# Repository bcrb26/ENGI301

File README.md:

# ENGI301
# "Repository for ENGI301 course work"
# PROJECT BAKI 
# woohoo
# Breakthrough Automated [Redacted] Instrument

# I forgot how to use github lol

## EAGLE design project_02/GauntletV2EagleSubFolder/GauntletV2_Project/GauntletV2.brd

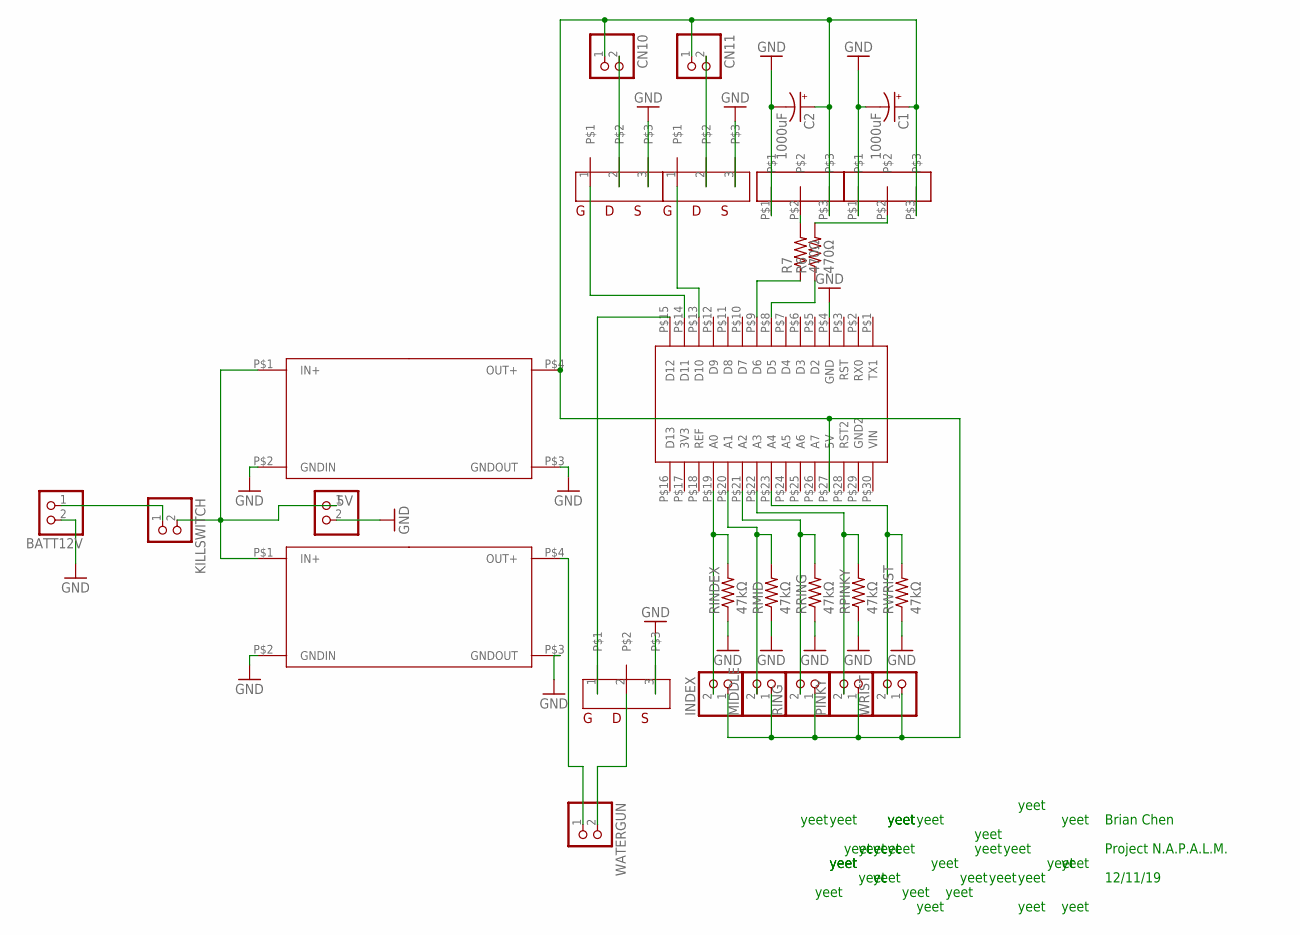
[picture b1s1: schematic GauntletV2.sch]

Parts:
5VBUCK, 6VBUCK: LM2596BUCK
BATT12V: JST_2PIN-THM-RA; JST-PH-2-THM-RA
C1, C2: 1000uF; E5-10,5
CN10, CN11: JST_2PIN-THM-RA; JST-PH-2-THM-RA
GUNMOSFET: TO254P1052X465X1989-3
INDEX: JST_2PIN-THM-RA; JST-PH-2-THM-RA
KILLSWITCH: JST_2PIN-THM-RA; JST-PH-2-THM-RA
MIDDLE: JST_2PIN-THM-RA; JST-PH-2-THM-RA
NANO: NANOV3
PINKY: JST_2PIN-THM-RA; JST-PH-2-THM-RA
R6, R7: 470Ω; 0207/9
RINDEX: 47kΩ; 0207/9
RING: JST_2PIN-THM-RA; JST-PH-2-THM-RA
RMID: 47kΩ; 0207/9
RPINKY: 47kΩ; 0207/9
RRING: 47kΩ; 0207/9
RWRIST: 47kΩ; 0207/9
U$4, U$5: TO254P1052X465X1989-3
U$7, U$8: 3WIRECONNECTOR
VOLTMETER: JST_2PIN-THM-RA; JST-PH-2-THM-RA
WATERGUN: JST_2PIN-THM-RA; JST-PH-2-THM-RA
WRIST: JST_2PIN-THM-RA; JST-PH-2-THM-RA

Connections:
5V: 5VBUCK.P$1 (IN+), 6VBUCK.P$1 (IN+), KILLSWITCH.2 (1), VOLTMETER.1 (2)
GND: 5VBUCK.P$2 (GNDIN), 5VBUCK.P$3 (GNDOUT), 6VBUCK.P$2 (GNDIN), 6VBUCK.P$3 (GNDOUT), BATT12V.2 (1), C1.-, C2.-, GUNMOSFET.3, NANO.P$4 (GND), RINDEX.1, RMID.1, RPINKY.1, RRING.1, RWRIST.1, U$4.3, U$5.3, U$7.P$1, U$8.P$1, VOLTMETER.2 (1)
unnamed: BATT12V.1 (2), KILLSWITCH.1 (2)
unnamed: 5VBUCK.P$4 (OUT+), C1.+, C2.+, CN10.1 (2), CN11.1 (2), INDEX.1 (2), MIDDLE.1 (2), NANO.P$27 (5V), PINKY.1 (2), RING.1 (2), U$7.P$3, U$8.P$3, WRIST.1 (2)
unnamed: R7.2, U$7.P$2
unnamed: GUNMOSFET.2, WATERGUN.2 (1)
unnamed: 6VBUCK.P$4 (OUT+), WATERGUN.1 (2)
unnamed: GUNMOSFET.1, NANO.P$15 (D12)
unnamed: INDEX.2 (1), NANO.P$19 (A0), RINDEX.2
unnamed: NANO.P$23 (A4), RWRIST.2, WRIST.2 (1)
unnamed: NANO.P$21 (A2), RING.2 (1), RRING.2
unnamed: MIDDLE.2 (1), NANO.P$20 (A1), RMID.2
unnamed: NANO.P$22 (A3), PINKY.2 (1), RPINKY.2
unnamed: NANO.P$14 (D11), U$5.1
unnamed: NANO.P$13 (D10), U$4.1
unnamed: CN10.2 (1), U$5.2
unnamed: CN11.2 (1), U$4.2
unnamed: NANO.P$9 (D6), R7.1
unnamed: R6.2, U$8.P$2
unnamed: NANO.P$8 (D5), R6.1

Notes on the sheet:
Brian Chen
Project N.A.P.A.L.M.
12/11/19
yeet

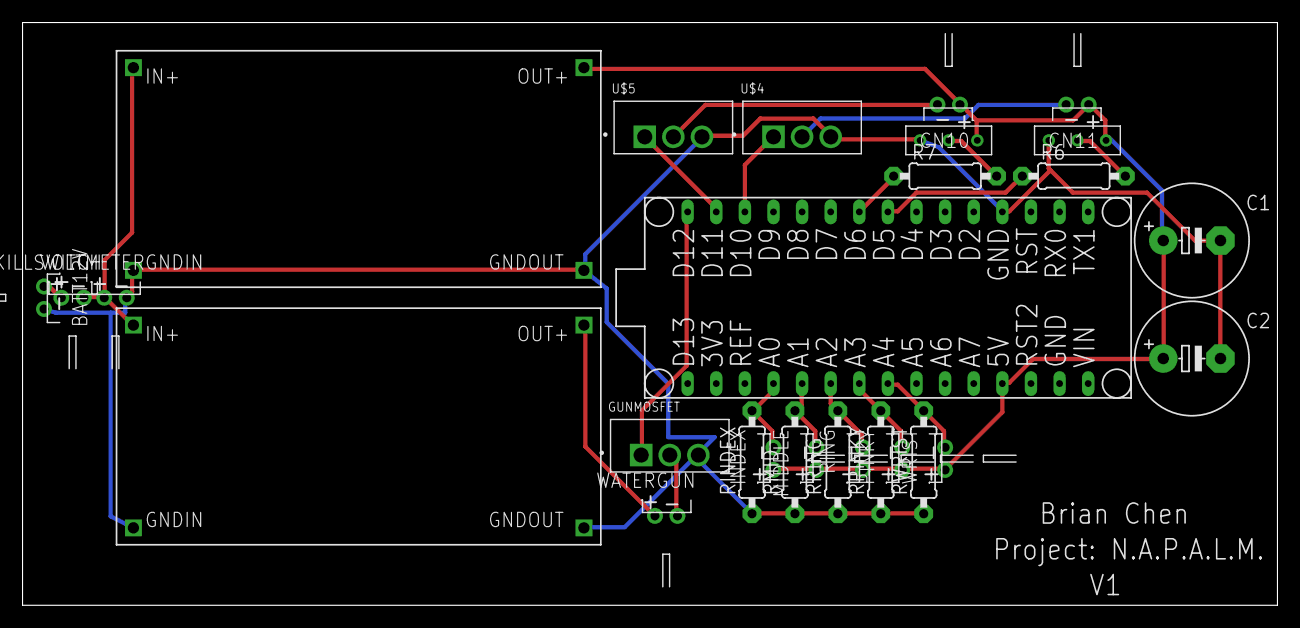
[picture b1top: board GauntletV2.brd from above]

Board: 2 copper layers, 111.4 x 51.7 mm, 28 parts (0 on the bottom side), 20 nets.

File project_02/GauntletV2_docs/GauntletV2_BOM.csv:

"Part;""Value"";""Device"";""Package"";""Description"";"""";",,
"5VBUCK;""LM2596BUCK"";""LM2596BUCK"";""LM2596BUCK"";"""";"""";",,
"6VBUCK;""LM2596BUCK"";""LM2596BUCK"";""LM2596BUCK"";"""";"""";",,
"BATT12V;"""";""JST_2PIN-THM-RA"";""JST-PH-2-THM-RA"";""JST 2-Pin Connectors of various flavors"";"""";",,
"C1;""1000uF"";""CPOL-USE5-10.5"";""E5-10","5"";""POLARIZED CAPACITOR"," American symbol"";"""";"
"C2;""1000uF"";""CPOL-USE5-10.5"";""E5-10","5"";""POLARIZED CAPACITOR"," American symbol"";"""";"
"CN10;"""";""JST_2PIN-THM-RA"";""JST-PH-2-THM-RA"";""JST 2-Pin Connectors of various flavors"";"""";",,
"CN11;"""";""JST_2PIN-THM-RA"";""JST-PH-2-THM-RA"";""JST 2-Pin Connectors of various flavors"";"""";",,
"GUNMOSFET;""TO254P1052X465X1989-3"";""TO254P1052X465X1989-3"";""TO254P1052X465X1989-3"";"""";"""";",,
"INDEX;"""";""JST_2PIN-THM-RA"";""JST-PH-2-THM-RA"";""JST 2-Pin Connectors of various flavors"";"""";",,
"KILLSWITCH;"""";""JST_2PIN-THM-RA"";""JST-PH-2-THM-RA"";""JST 2-Pin Connectors of various flavors"";"""";",,
"MIDDLE;"""";""JST_2PIN-THM-RA"";""JST-PH-2-THM-RA"";""JST 2-Pin Connectors of various flavors"";"""";",,
"NANO;""NANOV3"";""NANOV3"";""NANOV3"";"""";"""";",,
"PINKY;"""";""JST_2PIN-THM-RA"";""JST-PH-2-THM-RA"";""JST 2-Pin Connectors of various flavors"";"""";",,
"R6;""470Ω"";""R-US_0207/9"";""0207/9"";""RESISTOR"," American symbol"";"""";",
"R7;""470Ω"";""R-US_0207/9"";""0207/9"";""RESISTOR"," American symbol"";"""";",
"RINDEX;""47kΩ"";""R-US_0207/9"";""0207/9"";""RESISTOR"," American symbol"";"""";",
"RING;"""";""JST_2PIN-THM-RA"";""JST-PH-2-THM-RA"";""JST 2-Pin Connectors of various flavors"";"""";",,
"RMID;""47kΩ"";""R-US_0207/9"";""0207/9"";""RESISTOR"," American symbol"";"""";",
"RPINKY;""47kΩ"";""R-US_0207/9"";""0207/9"";""RESISTOR"," American symbol"";"""";",
"RRING;""47kΩ"";""R-US_0207/9"";""0207/9"";""RESISTOR"," American symbol"";"""";",
"RWRIST;""47kΩ"";""R-US_0207/9"";""0207/9"";""RESISTOR"," American symbol"";"""";",
"U$4;""TO254P1052X465X1989-3"";""TO254P1052X465X1989-3"";""TO254P1052X465X1989-3"";"""";"""";",,
"U$5;""TO254P1052X465X1989-3"";""TO254P1052X465X1989-3"";""TO254P1052X465X1989-3"";"""";"""";",,
"U$7;""3WIRECONNECTOR"";""3WIRECONNECTOR"";""3WIRECONNECTOR"";"""";"""";",,
"U$8;""3WIRECONNECTOR"";""3WIRECONNECTOR"";""3WIRECONNECTOR"";"""";"""";",,
"VOLTMETER;"""";""JST_2PIN-THM-RA"";""JST-PH-2-THM-RA"";""JST 2-Pin Connectors of various flavors"";"""";",,
"WATERGUN;"""";""JST_2PIN-THM-RA"";""JST-PH-2-THM-RA"";""JST 2-Pin Connectors of various flavors"";"""";",,
"WRIST;"""";""JST_2PIN-THM-RA"";""JST-PH-2-THM-RA"";""JST 2-Pin Connectors of various flavors"";"""";",,

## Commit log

2019-09-15 091519 Added #woohoo
2019-09-16 Acronym Full Name
2019-10-07 adding simple_calc to pocketbeagle local repository
2019-10-07 changed name
2019-11-21 Added some stuff to the main README
2019-11-21 created and added baki README
2019-11-21 FINALLY added the proposal powerpoint to the directory
2019-11-21 deleted test.md
2019-11-21 Added Python script and Fritzing diagram
2019-11-21 Added trackbar_test.py for color calibration - baki.py does not auto calibrate for target color
2019-11-21 added build and operation instructions to README
2019-11-28 Project II Proposal
2019-12-02 Added Eagle Subfolder and test library
2019-12-02 Added a buncha test files - test device creation
2019-12-12 The whole Eagle project, basically. Libraries, gerber files, project files, schematics, board are all in here one way or another
2019-12-12 Added CSV, PDF, and README
